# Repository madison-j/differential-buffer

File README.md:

# Quad channel differential buffer board

Set of four differential op-amps (AD8421); 10MHz bandwidth, low noise, variable gain settable with a resistor.

Idea here is to buffer monitor channels at the computer without introducing ground loops.

A set of three boards is available from OSHPark for $95; you can also send the gerbers to be manufactured at your board house of choice!

https://oshpark.com/shared_projects/IT3hNDoY

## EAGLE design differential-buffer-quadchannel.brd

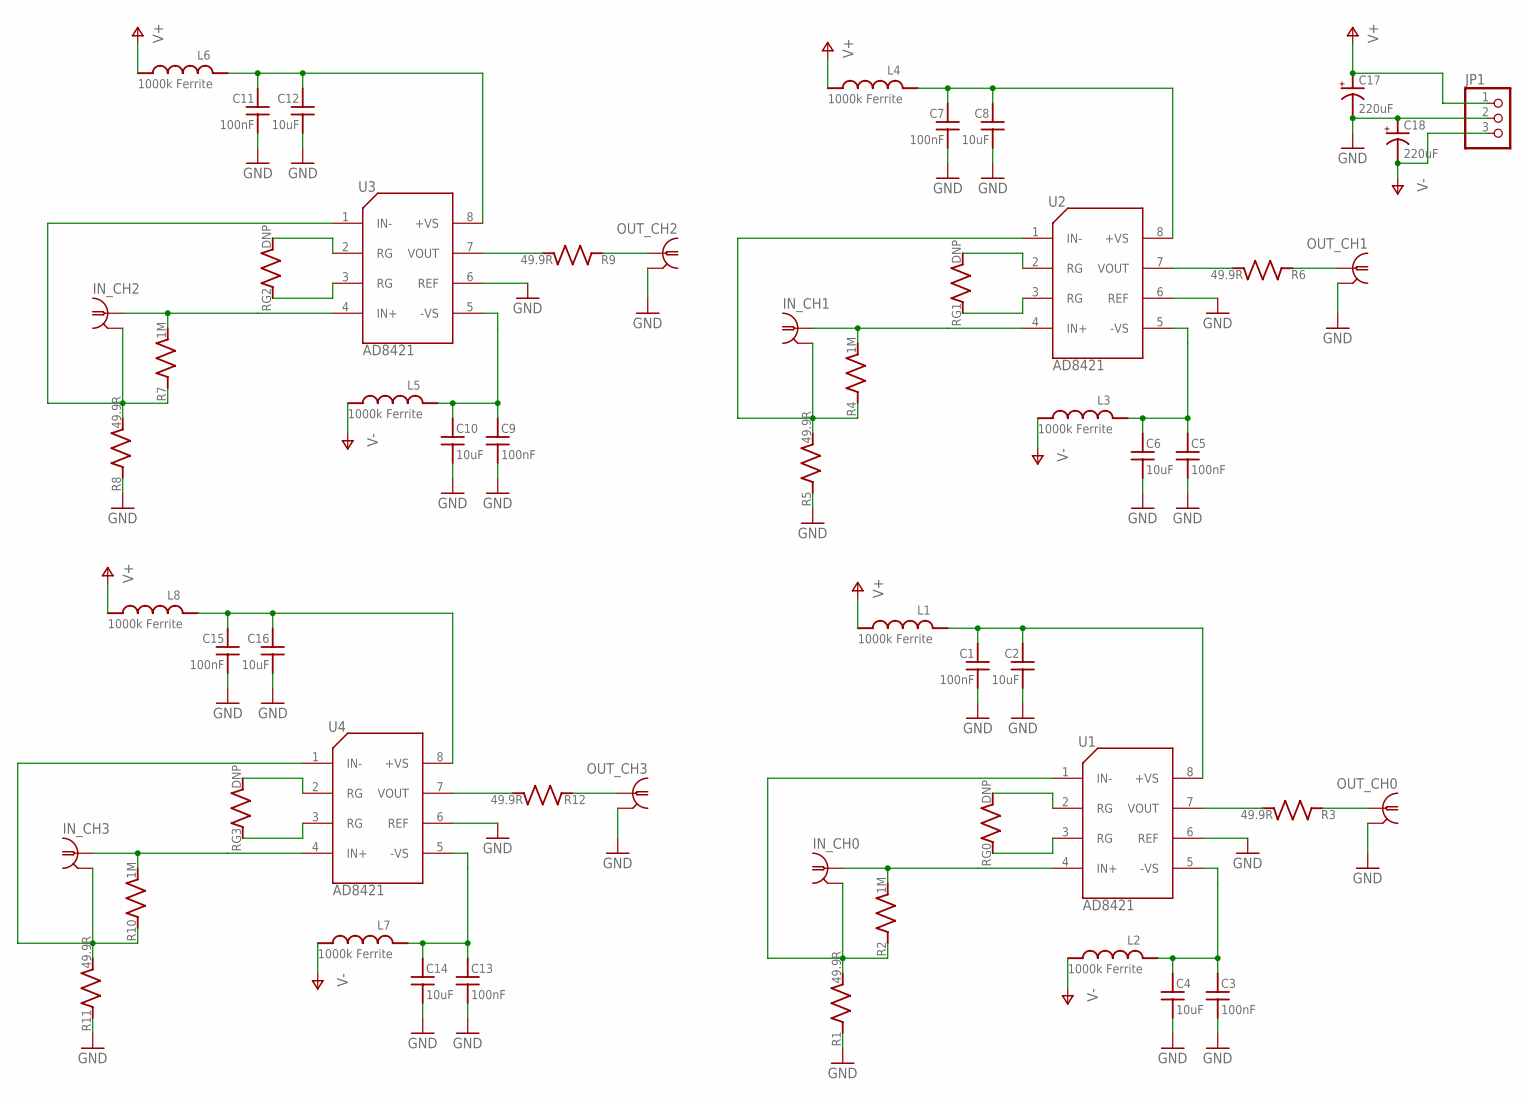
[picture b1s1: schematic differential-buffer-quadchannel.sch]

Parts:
C1, C3, C5, C7, C9, C11, C13, C15: 100nF; C_MLCC_0603; PARTNO 1276-1936-1-ND
C2, C4, C6, C8, C10, C12, C14, C16: 10uF; C_MLCC_0805; PARTNO 445-14417-1-ND
C17, C18: 220uF; PANASONIC_F; PARTNO PCE3955CT-ND
IN_CH0, IN_CH1, IN_CH2, IN_CH3: BNC-H; BNC90; PARTNO A32260-ND
JP1: PINHD-1X3; 1X03; PARTNO WM4201-ND
L1, L2, L3, L4, L5, L6, L7, L8: 1000k Ferrite; L_FERRITE_0603; PARTNO 445-1548-1-ND
OUT_CH0, OUT_CH1, OUT_CH2, OUT_CH3: BNC-H; BNC90; PARTNO A32260-ND
R1, R3, R5, R6, R8, R9, R11, R12: 49.9R; R_0603; PARTNO P49.9HCT-ND
R2, R4, R7, R10: 1M; R_0603; PARTNO P1.00MHCT-ND
RG0, RG1, RG2, RG3: DNP; R_0402
U1, U2, U3, U4: AD8421; SOIC-8; PARTNO AD8421ARZ-R7CT-ND

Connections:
GND: C1.P$2 (2), C2.P$2 (2), C3.P$2 (2), C4.P$2 (2), C5.P$2 (2), C6.P$2 (2), C7.P$2 (2), C8.P$2 (2), C9.P$2 (2), C10.P$2 (2), C11.P$2 (2), C12.P$2 (2), C13.P$2 (2), C14.P$2 (2), C15.P$2 (2), C16.P$2 (2), C17.-, C18.+, JP1.2, OUT_CH0.2, OUT_CH1.2, OUT_CH2.2, OUT_CH3.2, R1.P$1 (1), R5.P$1 (1), R8.P$1 (1), R11.P$1 (1), U1.6 (REF), U2.6 (REF), U3.6 (REF), U4.6 (REF)
unnamed: OUT_CH0.1, R3.P$1 (1)
unnamed: R3.P$2 (2), U1.7 (VOUT)
unnamed: C1.P$1 (1), C2.P$1 (1), L1.P$1 (1), U1.8 (+VS)
unnamed: RG0.P$1 (1), U1.3 (RG)
unnamed: RG0.P$2 (2), U1.2 (RG)
unnamed: IN_CH1.1, R4.P$2 (2), U2.4 (IN+)
unnamed: IN_CH1.2, R4.P$1 (1), R5.P$2 (2), U2.1 (IN-)
unnamed: OUT_CH1.1, R6.P$1 (1)
unnamed: R6.P$2 (2), U2.7 (VOUT)
unnamed: C5.P$1 (1), C6.P$1 (1), L3.P$1 (1), U2.5 (-VS)
unnamed: C7.P$1 (1), C8.P$1 (1), L4.P$1 (1), U2.8 (+VS)
unnamed: RG1.P$1 (1), U2.3 (RG)
unnamed: RG1.P$2 (2), U2.2 (RG)
unnamed: IN_CH2.1, R7.P$2 (2), U3.4 (IN+)
unnamed: IN_CH2.2, R7.P$1 (1), R8.P$2 (2), U3.1 (IN-)
unnamed: OUT_CH2.1, R9.P$1 (1)
unnamed: R9.P$2 (2), U3.7 (VOUT)
unnamed: C9.P$1 (1), C10.P$1 (1), L5.P$1 (1), U3.5 (-VS)
unnamed: C11.P$1 (1), C12.P$1 (1), L6.P$1 (1), U3.8 (+VS)
unnamed: RG2.P$1 (1), U3.3 (RG)
unnamed: RG2.P$2 (2), U3.2 (RG)
unnamed: IN_CH3.1, R10.P$2 (2), U4.4 (IN+)
unnamed: IN_CH3.2, R10.P$1 (1), R11.P$2 (2), U4.1 (IN-)
unnamed: OUT_CH3.1, R12.P$1 (1)
unnamed: R12.P$2 (2), U4.7 (VOUT)
unnamed: C13.P$1 (1), C14.P$1 (1), L7.P$1 (1), U4.5 (-VS)
unnamed: C15.P$1 (1), C16.P$1 (1), L8.P$1 (1), U4.8 (+VS)
unnamed: RG3.P$1 (1), U4.3 (RG)
unnamed: RG3.P$2 (2), U4.2 (RG)
unnamed: IN_CH0.1, R2.P$2 (2), U1.4 (IN+)
unnamed: IN_CH0.2, R1.P$2 (2), R2.P$1 (1), U1.1 (IN-)
unnamed: C3.P$1 (1), C4.P$1 (1), L2.P$1 (1), U1.5 (-VS)
V+: C17.+, JP1.1, L1.P$2 (2), L4.P$2 (2), L6.P$2 (2), L8.P$2 (2)
V-: C18.-, JP1.3, L2.P$2 (2), L3.P$2 (2), L5.P$2 (2), L7.P$2 (2)

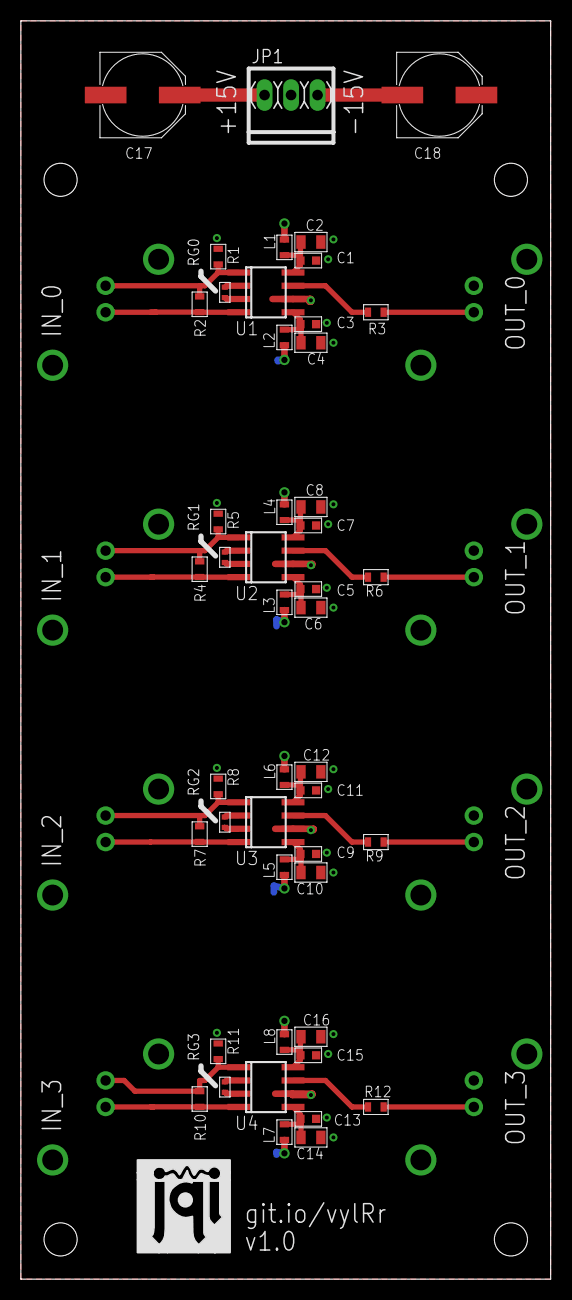
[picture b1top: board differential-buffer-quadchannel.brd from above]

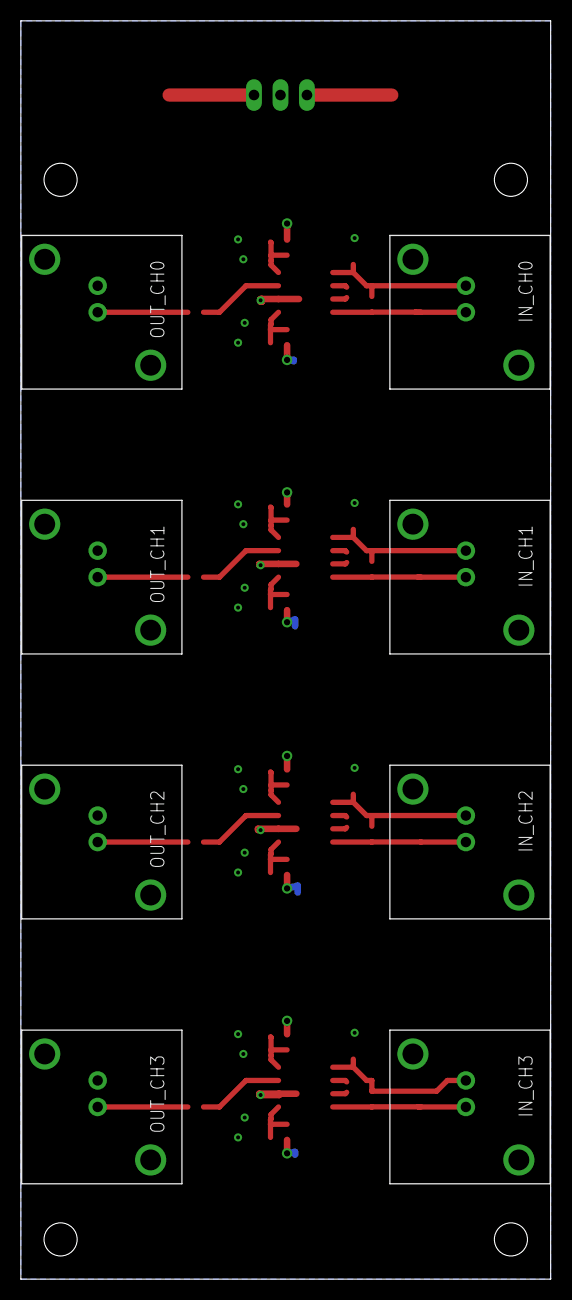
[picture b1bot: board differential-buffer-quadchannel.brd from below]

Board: 4 copper layers, 50.8 x 120.7 mm, 56 parts (8 on the bottom side), 35 nets.

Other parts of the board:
U$1: JQI_LOGO_NEGATIVE-SILKSCREEN

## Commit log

2017-03-05 Added part numbers
2019-02-06 changed RA BNC to vertical
2019-02-06 Readme update
